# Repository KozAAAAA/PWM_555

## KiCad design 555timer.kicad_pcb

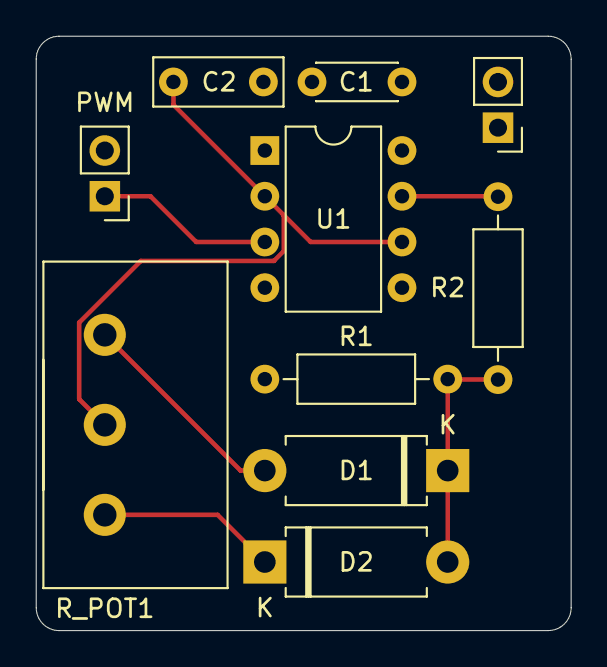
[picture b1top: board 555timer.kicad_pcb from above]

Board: 4 copper layers, 29.7 x 33.0 mm, 10 parts (0 on the bottom side), 8 nets.

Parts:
C1: 0.01uF; C_Disc_D4.3mm_W1.9mm_P5.00mm
C2: 47nF; C_Disc_D7.0mm_W2.5mm_P5.00mm
D1, D2: D; D_DO-15_P10.16mm_Horizontal
IN: Conn_01x02_Female; PinHeader_1x02_P2.54mm_Vertical
PWM: PWM; PinHeader_1x02_P2.54mm_Vertical
R1: 1k; R_Axial_DIN0207_L6.3mm_D2.5mm_P10.16mm_Horizontal
R2: 12; R_Axial_DIN0207_L6.3mm_D2.5mm_P10.16mm_Horizontal
R_POT1: R_POT; Potentiometer_Alps_RK163_Single_Horizontal
U1: NE555P; DIP-8_W7.62mm

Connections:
GND: C1.2, C2.2, IN.2, PWM.2, U1.1
unnamed: C2.1, R_POT1.2, U1.2, U1.6
unnamed: D1.1, D2.2, R1.2, R2.1
unnamed: D1.2, R_POT1.1
unnamed: D2.1, R_POT1.3
unnamed: R2.2, U1.7
VCC: C1.1, IN.1, R1.1, U1.4, U1.8
VDC: PWM.1, U1.3

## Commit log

2021-12-23 First update
2021-12-24 Set the componnets and created a pcb rectangle
2021-12-27 Rounded the corners
2021-12-28 Added all the traces, power planes and rearenged the silkscreen text
2022-01-21 Chenge the place of the elements
